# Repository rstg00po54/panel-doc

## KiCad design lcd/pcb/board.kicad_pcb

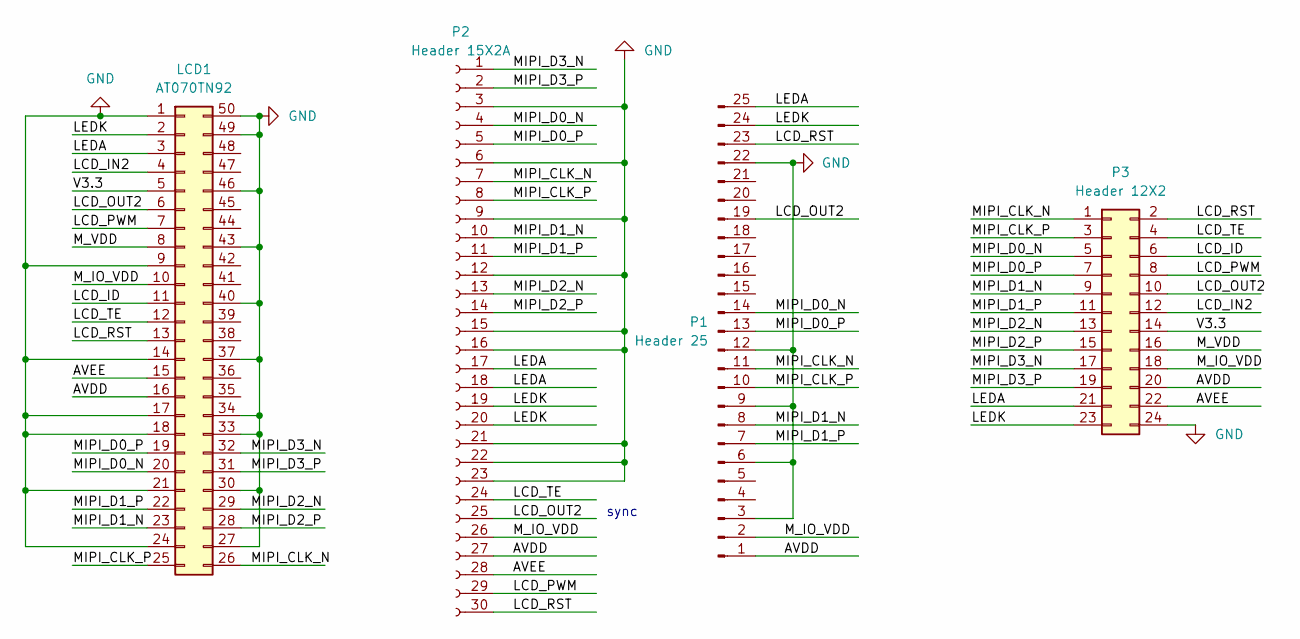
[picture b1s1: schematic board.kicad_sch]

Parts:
LCD1: AT070TN92; FPC-TOP50
P1: Header 25; FPC25-0.3-rev
P2: Header 15X2A; FPC30-0.3
P3: Header 12X2; HDR2X12

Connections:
/AVDD: LCD1.16, P1.1, P2.27, P3.20
/AVEE: LCD1.15, P2.28, P3.22
/LCD_ID: LCD1.11, P3.6
/LCD_IN2: LCD1.4, P3.12
/LCD_OUT2: LCD1.6, P1.19, P2.25, P3.10
/LCD_PWM: LCD1.7, P2.29, P3.8
/LCD_RST: LCD1.13, P1.23, P2.30, P3.2
/LCD_TE: LCD1.12, P2.24, P3.4
/LEDA: LCD1.3, P1.25, P2.17, P2.18, P3.21
/LEDK: LCD1.2, P1.24, P2.19, P2.20, P3.23
/MIPI_CLK_N: LCD1.26, P1.11, P2.7, P3.1
/MIPI_CLK_P: LCD1.25, P1.10, P2.8, P3.3
/MIPI_D0_N: LCD1.20, P1.14, P2.4, P3.5
/MIPI_D0_P: LCD1.19, P1.13, P2.5, P3.7
/MIPI_D1_N: LCD1.23, P1.8, P2.10, P3.9
/MIPI_D1_P: LCD1.22, P1.7, P2.11, P3.11
/MIPI_D2_N: LCD1.29, P2.13, P3.13
/MIPI_D2_P: LCD1.28, P2.14, P3.15
/MIPI_D3_N: LCD1.32, P2.1, P3.17
/MIPI_D3_P: LCD1.31, P2.2, P3.19
/M_IO_VDD: LCD1.10, P1.2, P2.26, P3.18
/M_VDD: LCD1.8, P3.16
/V3.3: LCD1.5, P3.14
GND: LCD1.1, LCD1.9, LCD1.14, LCD1.17, LCD1.18, LCD1.21, LCD1.24, LCD1.27, LCD1.30, LCD1.33, LCD1.34, LCD1.37, LCD1.40, LCD1.43, LCD1.46, LCD1.49, LCD1.50, P1.3, P1.6, P1.9, P1.12, P1.22, P2.3, P2.6, P2.9, P2.12, P2.15, P2.16, P2.21, P2.22, P2.23, P3.24

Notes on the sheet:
sync

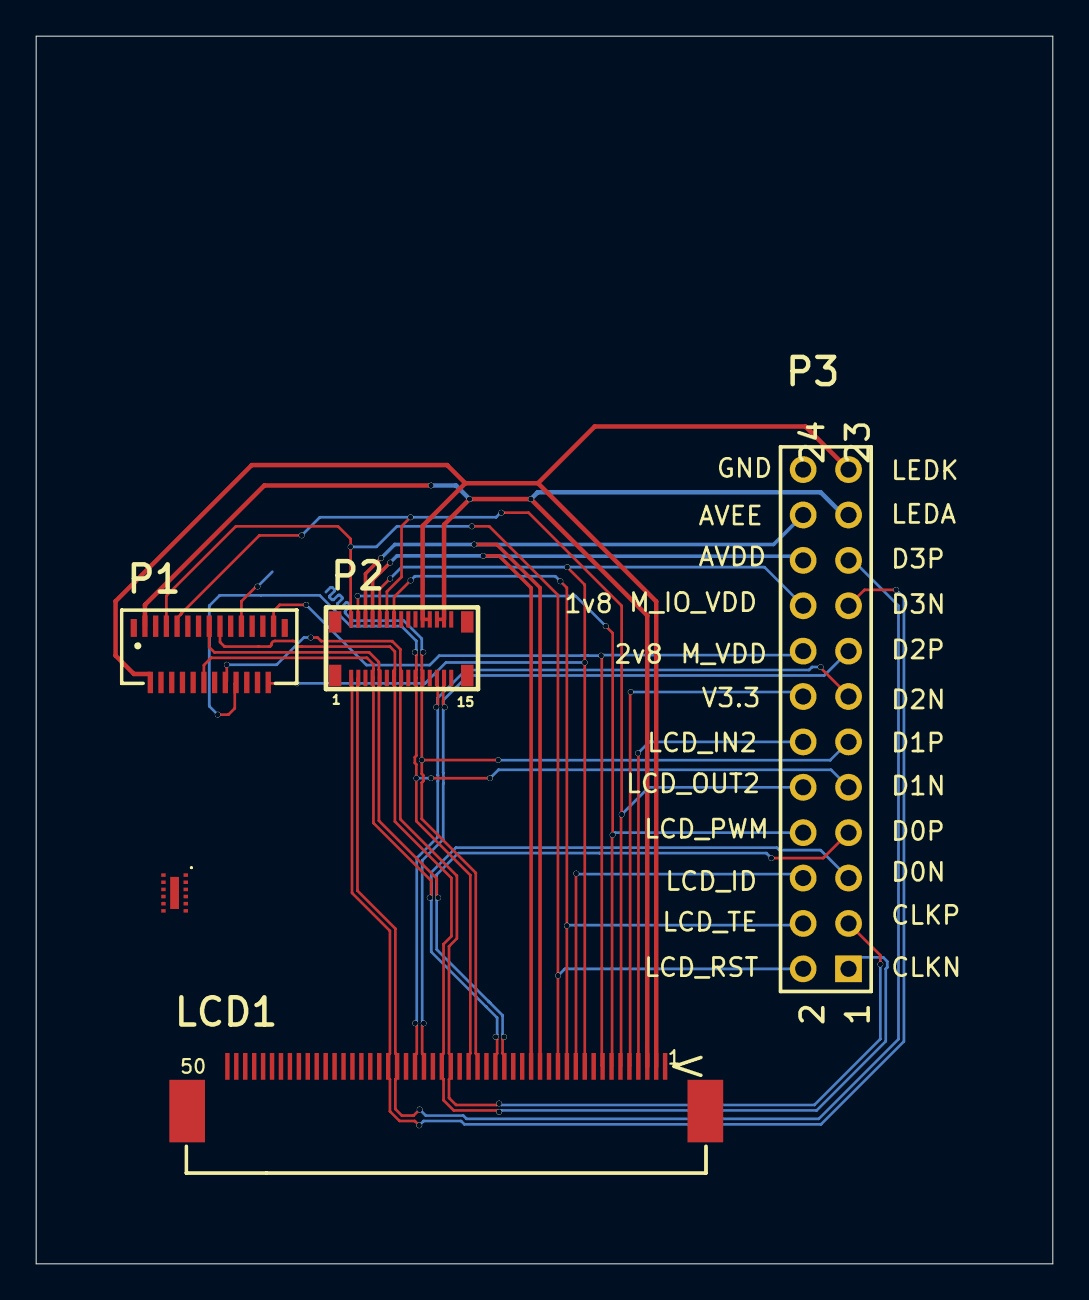
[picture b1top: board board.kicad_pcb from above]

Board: 2 copper layers, 56.9 x 68.7 mm, 4 parts (0 on the bottom side), 24 nets.

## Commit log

2026-01-29 init
2026-02-03 add panel
2026-03-02 3.1寸屏幕
2026-03-03 mcu panel
